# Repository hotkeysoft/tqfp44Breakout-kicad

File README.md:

# TQFP44 Breakout Board
Rev A October 2019

As simple as it gets.

Images
============
|Front                                                 | Back                                              |
|------------------------------------------------------|---------------------------------------------------|
|||

### Schematics (pdf)
- [Complete schematics](./img/schema.pdf)

### PCB Images (svg)
- [Top](./img/pcb-front.svg)
- [Bottom](./img/pcb-back.svg)

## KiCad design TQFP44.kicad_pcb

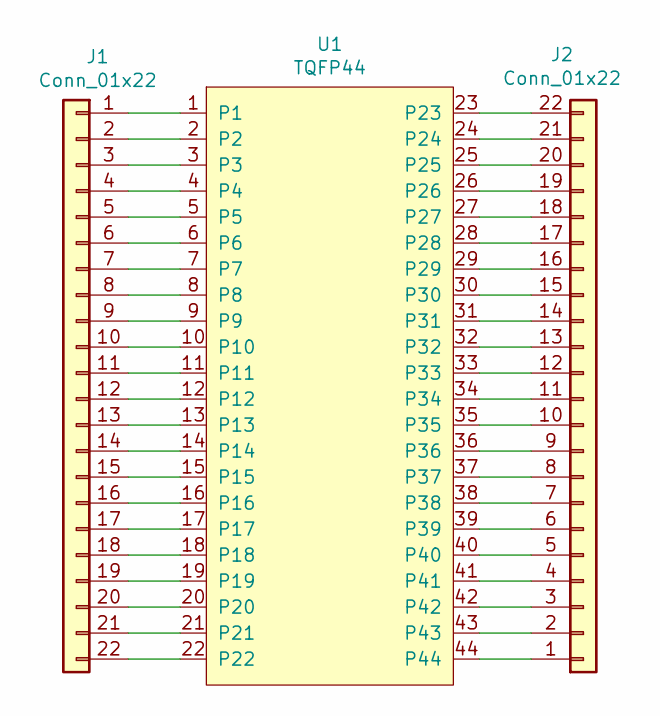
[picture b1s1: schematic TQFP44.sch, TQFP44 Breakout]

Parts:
J1, J2: Conn_01x22; PinHeader_1x22_P2.54mm_Vertical
U1: TQFP44; TQFP-44_10x10mm_P0.8mm

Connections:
unnamed: J1.1, U1.1
unnamed: J1.2, U1.2
unnamed: J1.3, U1.3
unnamed: J1.4, U1.4
unnamed: J1.5, U1.5
unnamed: J1.6, U1.6
unnamed: J1.7, U1.7
unnamed: J1.8, U1.8
unnamed: J1.9, U1.9
unnamed: J1.10, U1.10
unnamed: J1.11, U1.11
unnamed: J1.12, U1.12
unnamed: J1.13, U1.13
unnamed: J1.14, U1.14
unnamed: J1.15, U1.15
unnamed: J1.16, U1.16
unnamed: J1.17, U1.17
unnamed: J1.18, U1.18
unnamed: J1.19, U1.19
unnamed: J1.20, U1.20
unnamed: J1.21, U1.21
unnamed: J1.22, U1.22
unnamed: J2.1, U1.44
unnamed: J2.2, U1.43
unnamed: J2.3, U1.42
unnamed: J2.4, U1.41
unnamed: J2.5, U1.40
unnamed: J2.6, U1.39
unnamed: J2.7, U1.38
unnamed: J2.8, U1.37
unnamed: J2.9, U1.36
unnamed: J2.10, U1.35
unnamed: J2.11, U1.34
unnamed: J2.12, U1.33
unnamed: J2.13, U1.32
unnamed: J2.14, U1.31
unnamed: J2.15, U1.30
unnamed: J2.16, U1.29
unnamed: J2.17, U1.28
unnamed: J2.18, U1.27
unnamed: J2.19, U1.26
unnamed: J2.20, U1.25
unnamed: J2.21, U1.24
unnamed: J2.22, U1.23

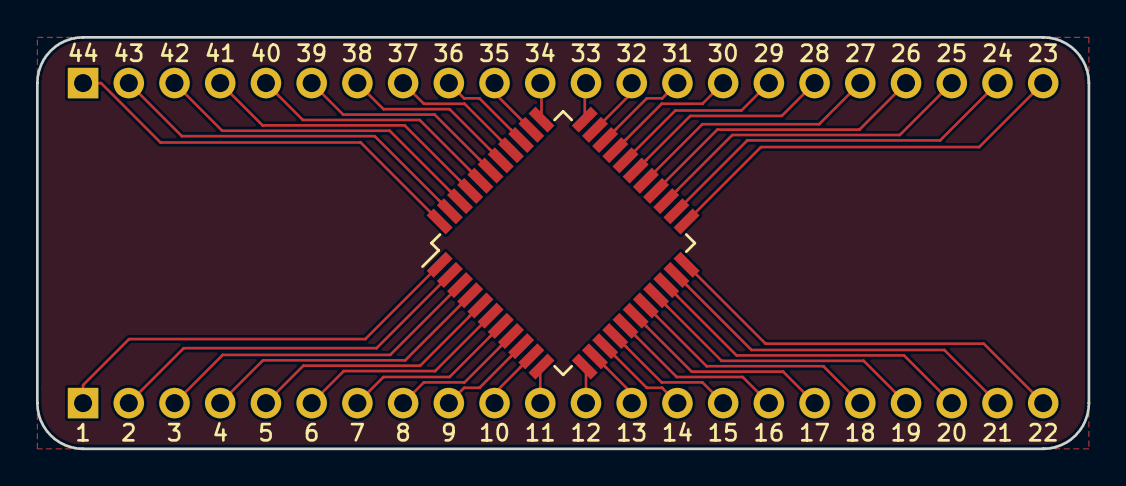
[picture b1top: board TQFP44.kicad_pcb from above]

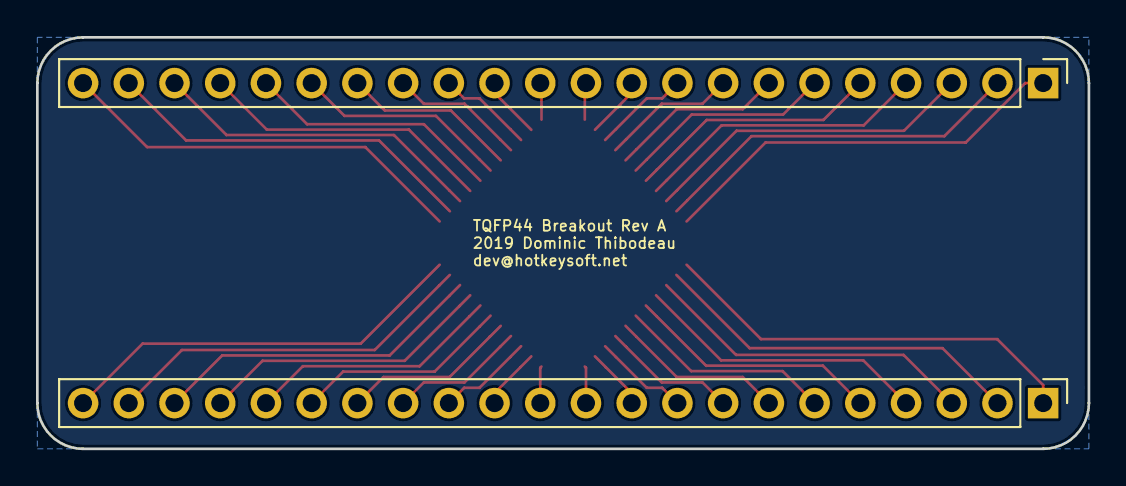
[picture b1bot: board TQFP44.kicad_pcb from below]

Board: 2 copper layers, 58.4 x 22.9 mm, 3 parts (2 on the bottom side), 44 nets.

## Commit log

2019-10-24 TQFT44 Breakout board
2020-07-11 Cleanup, added images
2020-07-11 Added README.md
2020-07-11 Remove fab dir
2020-07-11 Updated renders
2020-07-11 Create LICENSE
